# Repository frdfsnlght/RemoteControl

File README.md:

##Current consumption:

* Sleep: 9mA
* Deep sleep: 3.3mA

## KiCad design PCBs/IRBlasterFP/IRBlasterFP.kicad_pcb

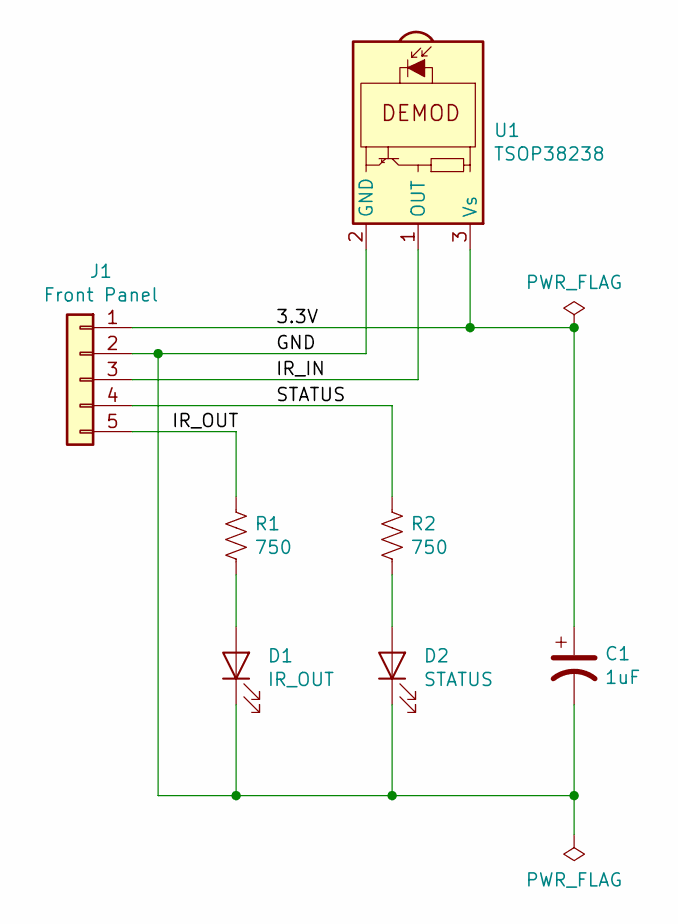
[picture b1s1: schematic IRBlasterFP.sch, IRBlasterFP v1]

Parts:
C1: 1uF; CP_Radial_D5.0mm_P2.50mm
D1: IR_OUT; LED_D3.0mm
D2: STATUS; LED_D3.0mm
J1: Front Panel; Pin_Header_Straight_1x05_Pitch2.54mm
R1, R2: 750; R_Axial_DIN0204_L3.6mm_D1.6mm_P1.90mm_Vertical
U1: TSOP38238; Pin_Header_Straight_1x03_Pitch2.54mm

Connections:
/3.3V: C1.1, J1.1, U1.3 (Vs)
/GND: C1.2, D1.1 (K), D2.1 (K), J1.2, U1.2 (GND)
/IR_IN: J1.3, U1.1 (OUT)
/IR_OUT: J1.5, R1.1
/STATUS: J1.4, R2.1
unnamed: D1.2 (A), R1.2
unnamed: D2.2 (A), R2.2

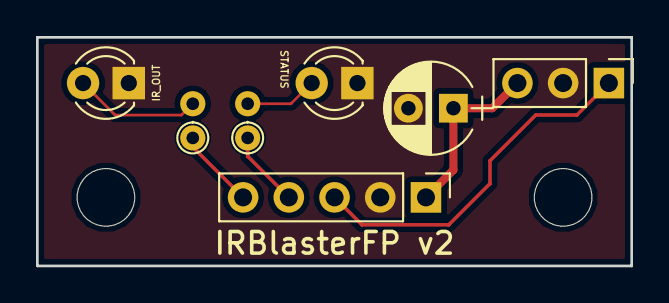
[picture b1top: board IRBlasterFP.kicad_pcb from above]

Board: 2 copper layers, 33.0 x 12.7 mm, 7 parts (0 on the bottom side), 7 nets.

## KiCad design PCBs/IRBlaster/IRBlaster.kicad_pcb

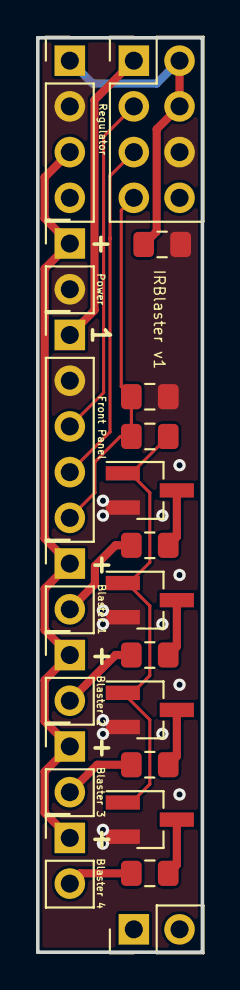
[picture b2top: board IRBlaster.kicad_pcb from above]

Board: 2 copper layers, 9.1 x 50.8 mm, 19 parts (0 on the bottom side), 16 nets.

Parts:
C1: 10uF; C_0805_2012Metric_Pad1.15x1.40mm_HandSolder
J1: Raspberry Pi; PinHeader_2x04_P2.54mm_Vertical
J2: Power; PinHeader_1x02_P2.54mm_Vertical
J3: Regulator; Pin_Header_Straight_1x04_Pitch2.54mm
J4: Front Panel; Pin_Header_Straight_1x05_Pitch2.54mm
J5: Blaster 1; PinHeader_1x02_P2.54mm_Vertical
J6: Blaster 2; PinHeader_1x02_P2.54mm_Vertical
J7: Blaster 3; PinHeader_1x02_P2.54mm_Vertical
J8: Blaster 4; PinHeader_1x02_P2.54mm_Vertical
Q1, Q2, Q3, Q4: IRLML6244; SOT-23_Handsoldering
R1: 10K; R_0805_2012Metric_Pad1.15x1.40mm_HandSolder
R2: 100; R_0805_2012Metric_Pad1.15x1.40mm_HandSolder
R3, R4, R5, R6: 0; R_0805_2012Metric_Pad1.15x1.40mm_HandSolder

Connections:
/3.3V: J1.1, J4.1
/5V: C1.1, J1.2, J1.4, J3.1
/12V: J2.1, J3.3, J5.1, J6.1, J7.1, J8.1
/GND: C1.2, J1.6, J2.2, J3.2, J4.2, Q1.2, Q2.2, Q3.2, Q4.2, R1.2
/IRB_1: J5.2, R3.1
/IRB_2: J6.2, R4.1
/IRB_3: J7.2, R5.1
/IRB_4: J8.2, R6.1
/IR_IN: J1.3, J4.3
/IR_OUT: J1.7, J4.5, R1.1, R2.2
/STATUS: J1.5, J4.4
unnamed: Q1.1, Q2.1, Q3.1, Q4.1, R2.1
unnamed: Q1.3, R3.2
unnamed: Q2.3, R4.2
unnamed: Q3.3, R5.2
unnamed: Q4.3, R6.2

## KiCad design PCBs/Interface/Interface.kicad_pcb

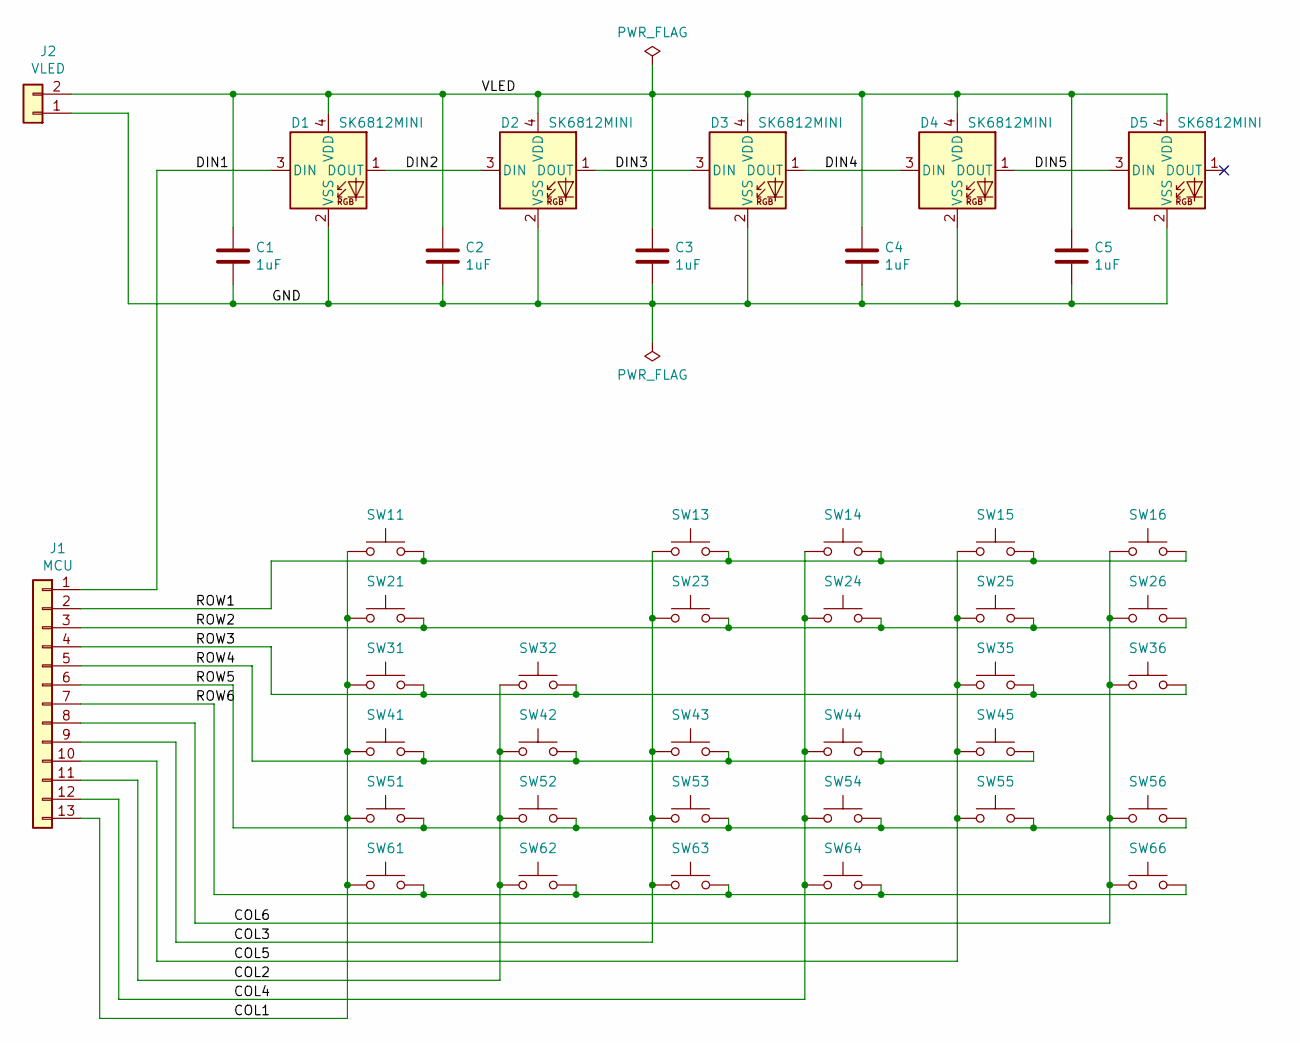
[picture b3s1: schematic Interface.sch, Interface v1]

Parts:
C1, C2, C3, C4, C5: 1uF; C_0805_HandSoldering
D1, D2, D3, D4, D5: SK6812MINI; PLCC4_3.5x3.5mm_P1.75mm
J1: MCU; SMD_Right_Socket_Strip_Angled_1x13_Pitch2.54mm
J2: VLED; SMD_Right_Socket_Strip_Angled_1x02_Pitch2.54mm
SW11, SW13, SW14, SW15, SW16, SW21, SW23, SW24, SW25, SW26, SW31, SW32, SW35, SW36, SW41, SW42, SW43, SW44, SW45, SW51, SW52, SW53, SW54, SW55, SW56, SW61, SW62, SW63, SW64, SW66: SW_Push; SMD_Tactile_Switch

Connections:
/COL1: J1.13, SW11.1, SW21.1, SW31.1, SW41.1, SW51.1, SW61.1
/COL2: J1.11, SW32.1, SW42.1, SW52.1, SW62.1
/COL3: J1.9, SW13.1, SW23.1, SW43.1, SW53.1, SW63.1
/COL4: J1.12, SW14.1, SW24.1, SW44.1, SW54.1, SW64.1
/COL5: J1.10, SW15.1, SW25.1, SW35.1, SW45.1, SW55.1
/COL6: J1.8, SW16.1, SW26.1, SW36.1, SW56.1, SW66.1
/DIN1: D1.3 (DIN), J1.1
/DIN2: D1.1 (DOUT), D2.3 (DIN)
/DIN3: D2.1 (DOUT), D3.3 (DIN)
/DIN4: D3.1 (DOUT), D4.3 (DIN)
/DIN5: D4.1 (DOUT), D5.3 (DIN)
/GND: C1.2, C2.2, C3.2, C4.2, C5.2, D1.2 (VSS), D2.2 (VSS), D3.2 (VSS), D4.2 (VSS), D5.2 (VSS), J2.1
/ROW1: J1.2, SW11.2, SW13.2, SW14.2, SW15.2, SW16.2
/ROW2: J1.3, SW21.2, SW23.2, SW24.2, SW25.2, SW26.2
/ROW3: J1.4, SW31.2, SW32.2, SW35.2, SW36.2
/ROW4: J1.5, SW41.2, SW42.2, SW43.2, SW44.2, SW45.2
/ROW5: J1.6, SW51.2, SW52.2, SW53.2, SW54.2, SW55.2, SW56.2
/ROW6: J1.7, SW61.2, SW62.2, SW63.2, SW64.2, SW66.2
/VLED: C1.1, C2.1, C3.1, C4.1, C5.1, D1.4 (VDD), D2.4 (VDD), D3.4 (VDD), D4.4 (VDD), D5.4 (VDD), J2.2

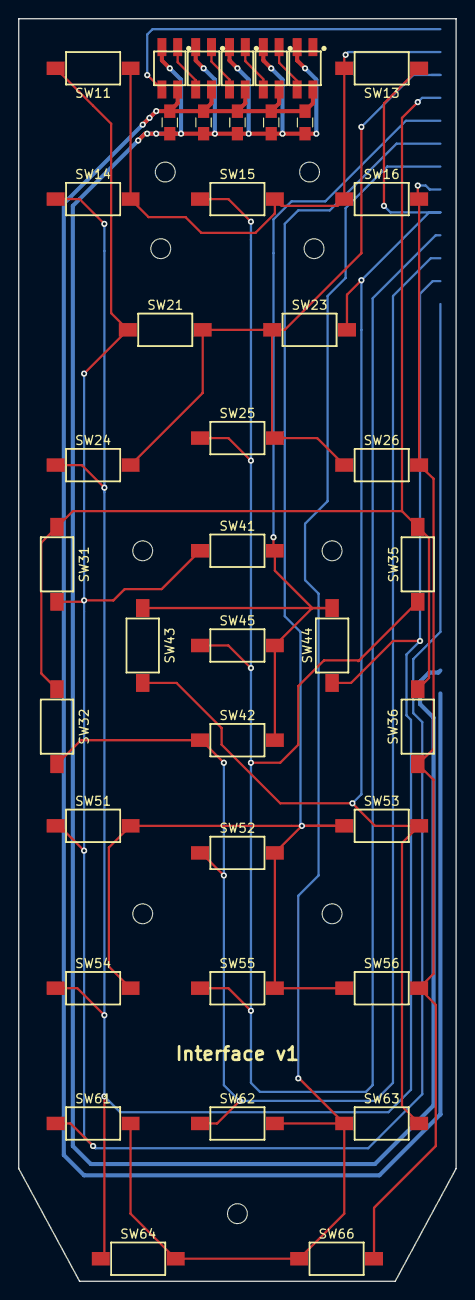
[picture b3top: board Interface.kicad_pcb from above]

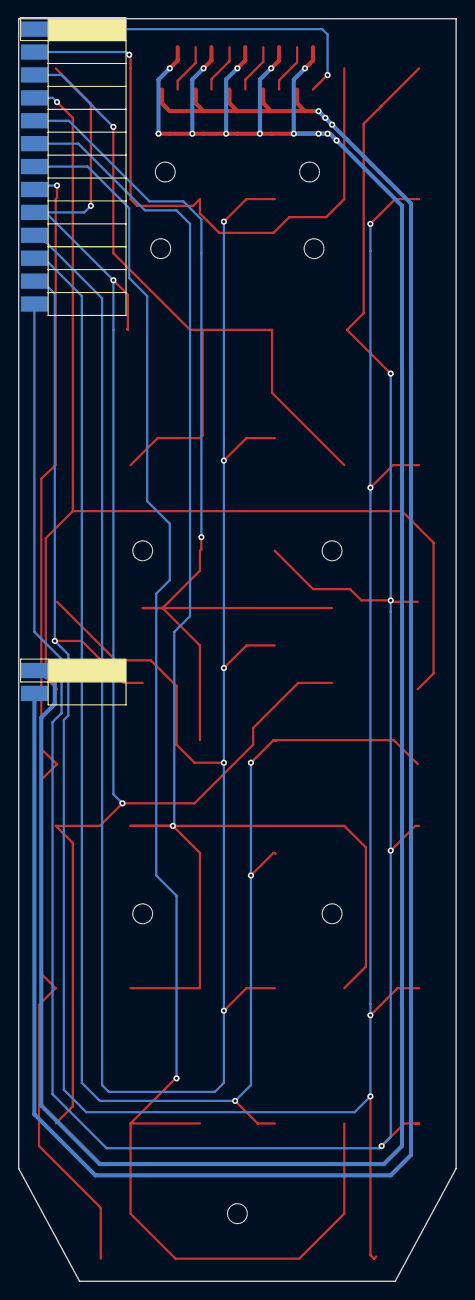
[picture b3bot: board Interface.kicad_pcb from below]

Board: 2 copper layers, 48.5 x 140.0 mm, 42 parts (2 on the bottom side), 19 nets.

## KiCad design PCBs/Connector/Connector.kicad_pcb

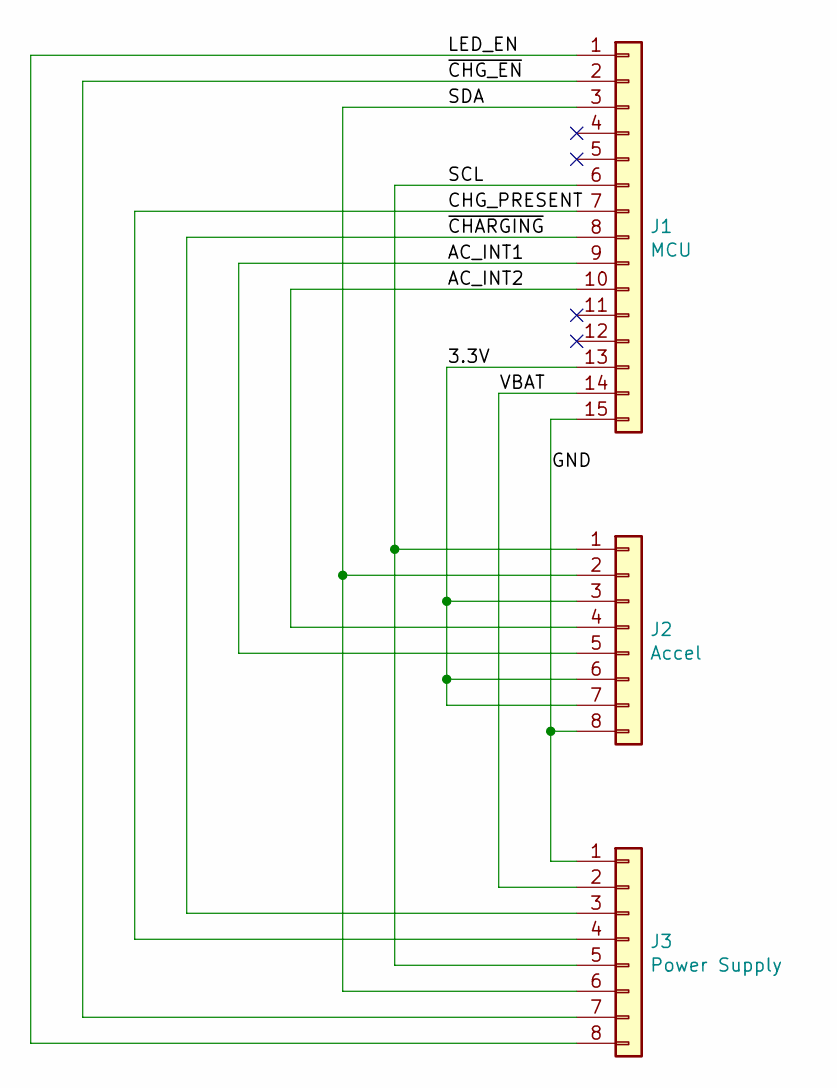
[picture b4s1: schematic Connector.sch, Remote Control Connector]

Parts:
J1: MCU; Pin_Header_Straight_1x15_Pitch2.54mm
J2: Accel; Pin_Header_Straight_1x08_Pitch2.54mm
J3: Power Supply; Pin_Header_Straight_1x08_Pitch2.54mm

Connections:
/3.3V: J1.13, J2.3, J2.6, J2.7
/AC_INT1: J1.9, J2.5
/AC_INT2: J1.10, J2.4
/CHG_PRESENT: J1.7, J3.4
/GND: J1.15, J2.8, J3.1
/LED_EN: J1.1, J3.8
/SCL: J1.6, J2.1, J3.5
/SDA: J1.3, J2.2, J3.6
/VBAT: J1.14, J3.2
/~CHARGING: J1.8, J3.3
/~CHG_EN: J1.2, J3.7

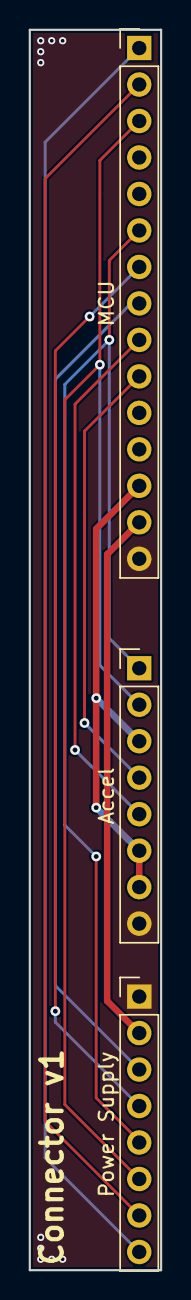
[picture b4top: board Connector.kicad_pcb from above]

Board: 2 copper layers, 9.1 x 86.4 mm, 3 parts (0 on the bottom side), 11 nets.

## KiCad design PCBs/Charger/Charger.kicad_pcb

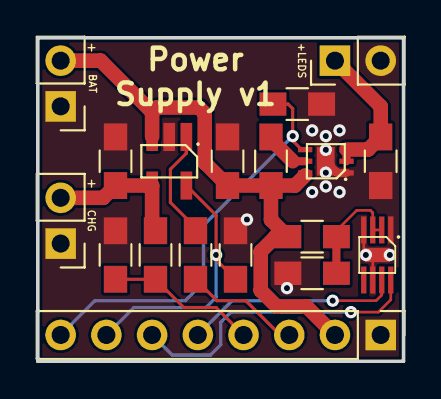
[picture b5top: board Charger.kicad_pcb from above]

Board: 2 copper layers, 20.3 x 18.0 mm, 18 parts (0 on the bottom side), 13 nets.

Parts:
C1, C2, C3: 10uF; R_0805_HandSoldering
C4: 1uF; R_0805_HandSoldering
J1: Battery; Pin_Header_Straight_1x02_Pitch2.54mm
J2: Charger; Pin_Header_Straight_1x02_Pitch2.54mm
J3: LEDs; Pin_Header_Straight_1x02_Pitch2.54mm
J4: MCU; Pin_Header_Straight_1x08_Pitch2.54mm
L1: 1uH; L_0805_HandSoldering
R1, R6: 1K; R_0805_HandSoldering
R2: 2K; R_0805_HandSoldering
R3: 2.2K; R_0805_HandSoldering
R4: 3.3K; R_0805_HandSoldering
R5: 10K; R_0805_HandSoldering
U1: MCP73831T-2; SOT-23-5_HandSoldering
U2: TPS61240; WSON6_2.1x2.1mm_Pitch0.65mm
U3: MAX17048; TDFN-T822+1

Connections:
/CELL: C4.1, R6.2, U3.2, U3.3
/CHG_PRESENT: J4.4, R3.2, R4.1
/L: L1.2, U2.5
/LED_EN: J4.8, R5.1, U2.4
/SCL: J4.5, U3.7
/SDA: J4.6, U3.8
/STAT: R1.2, U1.1
/VBAT: C2.1, J1.2, J4.2, L1.1, R6.1, U1.3, U2.6
/VCHG: C1.1, J2.2, R3.1, U1.4
/VLED: C3.1, J3.1, U2.2, U2.3
/~CHARGING: J4.3, R1.1
/~CHG_EN: J4.7, R2.1, U1.5
GND: C1.2, C2.2, C3.2, C4.2, J1.1, J2.1, J3.2, J4.1, R2.2, R4.2, R5.2, U1.2, U2.1, U2.EP, U3.1, U3.4, U3.6, U3.EP

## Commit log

2019-10-30 Started firmware
2019-10-30 Tweaked some comments.
2019-11-01 New circuits
2019-11-03 Changed
2019-11-05 Fixed some output pins.
2019-11-05 New datasheets
2019-11-05 New design and layout
2019-11-05 New designs
2019-11-07 Fixed logic bug, added timings
2019-11-07 Button tests, test layout
2019-11-07 Set emitter resistor values
2019-11-13 Server!
2019-11-13 Initial version
2019-11-13 New layout and buttons
2019-11-14 Added icons
2019-11-14 New spacers and tweaked button layout
2019-11-15 Fixed logging message
2019-11-15 Added VeraEdge driver
2019-11-15 Remove VeraEdge from TODO
2019-11-15 Started playing with gcode
2019-11-15 First version of hub enclosure
2019-11-15 Added datasheet for 3.mm jacks
2019-11-18 Datasheet for the switches
2019-11-18 Tweaks
2019-11-18 Started man interface board
2019-11-19 Rearranged code, added multikey handling, settings over bluetooth
2019-11-19 For setting remote settings over bluetooth
2019-11-19 Adjusted buttons to final positions before PCB manufacture
2019-11-19 Hopefullly final design before manufacture
2019-11-19 Removed debugging print
2019-11-19 New script for dealing with remote settings
2019-11-19 Renamed Charger to Power Supply
2019-11-20 Renamed Charger to PowerSupply
2019-11-20 Tweaked play/pause button
2019-11-20 Cleaned up attempt at gcode generation
2019-11-20 Ready for manufacture
2019-11-21 Added HTTClient driver
2019-11-21 Added HTTPEventServer driver
2019-11-22 Cleaned up bad libraries
2019-11-22 Added dimension lines
2019-11-22 No Longer needed
2019-11-22 Final version of hub case
2019-11-22 More work on remote case
2019-11-24 Renamed
2019-11-24 Fixed stupid bugs
2019-11-24 Added LIRC driver
2019-11-24 Hub ready for print
2019-11-24 Remote control bottom ready for print
2019-11-24 Fixed problems
2019-11-25 Ready for printing
2019-11-25 Fixed STLs
2019-11-25 Moved
2019-11-25 Return DotDict for nested dictionaries
2019-11-25 Attribute access for requests
2019-11-26 Added light pipe tool
2019-11-26 Added some test pieces and tweaked the buttons
2019-11-26 Added initial states, improved Lirc driver, tweaks
2019-11-26 Checked in my home configuration as sample config
2019-11-26 Added deep sleep and saving settings to flash
2019-11-26 Updated to match firmware
2019-11-27 Added triggerGenericEvent, fixes bugs
2019-11-28 Fixed menu button
2019-11-28 Fixed NVM write size bug
2019-11-28 Ready to print TPU buttons
2019-11-28 Renamed and tweaked stuff
2019-12-01 Removed stupid fuel gauge, added neopixel patterns, fixed NVM saving
2019-12-01 New script to read button presses
2019-12-01 Removed stupid fuel gauge
2019-12-01 Fixed bugs
2019-12-02 New TCPRemote driver
2019-12-03 Moved to new art folder
2019-12-03 Source for the client buttons
2019-12-03 Started Unity client
2019-12-04 Fixed bugs, added stuff
2019-12-04 Fixed decoding issue
2019-12-04 Updates to v0.2 of the client for Android and Windows
2019-12-04 Tweaked
2019-12-05 Added systemd configuration
2019-12-05 New event client
2019-12-05 New button client
2019-12-05 Fixed stop bug
2019-12-06 Fixed settings window not opening on first press, small UI tweaks, v0.3
2019-12-10 Added version label, handle app pausing
2019-12-11 Added SamsungTV driver
2019-12-12 Changed decoupling cap values
2019-12-13 Added LED debugging, changed deep/sleep conditions
2019-12-13 Moved writing LED characteristic to internal thread
2019-12-18 Changed spacer thickness
2019-12-18 Added ledBrightness, deep sleep debugging, fix for charging status
2019-12-19 Fixed time
2021-03-25 Bump pyyaml from 5.1.2 to 5.4 in /server
    Bumps [pyyaml](https://github.com/yaml/pyyaml) from 5.1.2 to 5.4.
    - [Release notes](https://github.com/yaml/pyyaml/releases)
    - [Changelog](https://github.com/yaml/pyyaml/blob/master/CHANGES)
    - [Commits](https://github.com/yaml/pyyaml/compare/5.1.2...5.4)
2021-11-21 Checking in all past changes
2021-11-22 New MQTT driver
2021-11-22 Make use of new MQTT driver and disable old theater related stuff
2022-01-04 Added exception handling to configuration loading
2022-01-04 Fixed interval handling
2022-01-04 New LED color handling
2022-01-04 Debugging for timer
2022-01-04 Added MQTT subscriptions
2022-01-04 Upped version ofg pyYaml for security reasons
2022-01-21 Added on connect message
2022-01-21 Renamed YamahaRXV device to YamahaAVR
2023-05-01 Bump flask from 1.1.1 to 2.3.2 in /server/lib/drivers/HTTPEventServer
    Bumps [flask](https://github.com/pallets/flask) from 1.1.1 to 2.3.2.
    - [Release notes](https://github.com/pallets/flask/releases)
    - [Changelog](https://github.com/pallets/flask/blob/main/CHANGES.rst)
    - [Commits](https://github.com/pallets/flask/compare/1.1.1...2.3.2)
    ---
    updated-dependencies:
2025-09-03 PJ only setup, Denon AVR, Roku tweaks
